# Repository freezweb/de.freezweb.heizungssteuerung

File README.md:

# de.freezweb.heizungssteuerung

Heizungssteuerung auf Revolution Pi Connect 4 mit Anbindung an Home Assistant (MQTT).

Komplette Spezifikation: siehe [LASTENHEFT.md](LASTENHEFT.md).

## Komponenten
- **Hauptsteuerung** Heizungsraum (RevPi #1, `10.1.25.10`)
- **Slave-Steuerung** Hauptkeller (RevPi #2, `10.1.25.11`, sp&auml;ter)
- **Visualisierung + History**: Home Assistant via MQTT-Discovery
- **Failsafe**: Witterungsgef&uuml;hrte Heizkurve bei MQTT-/HA-Ausfall

## Stack
- Python 3.11 (Asyncio)
- `revpimodio2` &mdash; RevPi-I/O
- `paho-mqtt` &mdash; HA-Kopplung
- `pymodbus` &mdash; W&auml;rmepumpen, Klima-Innenger&auml;te, Slave-CPU
- systemd (`Type=simple, Restart=on-failure`)

## Verzeichnisstruktur
```
src/heizung/        Hauptcode
config/             Live-Configs (gitignored, *.example committet)
pictory/            RevPi-PiCtory-Export
tests/              Pytest
deploy/             systemd-Unit + install/update Scripts
docs/               Hydraulik-, I/O- und MQTT-Doku
```

Wichtige Hardware-Planung:
- [docs/revpi-modulplanung.md](docs/revpi-modulplanung.md)
- [docs/io-belegung.md](docs/io-belegung.md)

## Quick start (Entwicklung)
```bash
python -m venv .venv
.venv\Scripts\activate
pip install -e .
cp config/settings.yaml.example config/settings.yaml
# Anpassen, dann:
python -m heizung
```

## Deployment auf RevPi
Siehe `deploy/install.sh`.

## Phasen-Plan
Siehe [LASTENHEFT.md Abschnitt 10](LASTENHEFT.md#10-phasen-plan-reihenfolge).

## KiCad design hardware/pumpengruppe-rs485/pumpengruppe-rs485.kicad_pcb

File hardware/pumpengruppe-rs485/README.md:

# Pumpengruppe RS485 KiCad-Projekt

RevA preliminary, Stand 2026-06-25.

Dieses Verzeichnis enthaelt den KiCad-Startentwurf fuer die dezentrale
Pumpengruppen-Platine:

- `pumpengruppe-rs485.kicad_pro`: KiCad-Projekt
- `pumpengruppe-rs485.kicad_sch`: Schaltplan mit lokalen Symbolen
- `pumpengruppe-rs485.kicad_pcb`: PCB-Grundlayout 160 x 110 mm
- `lib/`: lokale Symbole/Footprints
- `export-fab.ps1`: Gerber/Drill/BOM-Export per `kicad-cli`
- `fab/`: Zielordner fuer Fertigungsdaten

Aktueller Stand:

- Schaltplan/PCB laden in KiCad 10.0.4.
- Schaltplan enthaelt jetzt alle im PCB platzierten Hauptbauteile inklusive
  `F1`, `U5`, USB-C/USB-UART und schaltbarem RS485-Abschluss. Die lokalen
  Symbole haben benannte Pins; die Netznamen sind als sichtbare Texte an den
  Funktionspins gesetzt.
- Gerber/Drill/BOM lassen sich per `export-fab.ps1` erzeugen.
- USB-C-Serviceanschluss mit USB-UART-Funktion ist eingeplant.
- UART-Topologie im Schaltplan ist getrennt:
  `U6` USB-UART liegt nur auf ESP-UART0 (`ESP_U0RX`/`ESP_U0TX`) fuer
  Firmware/Debug. `U4` MAX3485 liegt separat auf dem RS485-UART
  (`RS485_UART_RX` = ESP GPIO16, `RS485_UART_TX` = ESP GPIO17,
  `RS485_DE` = ESP GPIO4). Nach dieser Korrektur muss die PCB-Datei in KiCad
  aus dem Schaltplan aktualisiert und das Routing fuer diese Netze neu gezogen
  werden; alte `UART_RX`/`UART_TX`-Routen im PCB duerfen nicht als
  Fertigungsstand gelten.
- ESP32 ist als WROOM-32D mit PCB-Antenne vorgesehen; Antennenseite am
  Platinenrand platzieren und Keepout freihalten.
- Relais werden nicht direkt vom ESP geschaltet: pro Relais sind 100R
  Gatewiderstand, 100k Pulldown, AO3400A-kompatibler NMOS, SS14-Freilaufdiode
  und Status-LED vorgesehen.
- Mischer ist als Hardware-Interlock geplant: `K2` schaltet nur die
  Mischerfreigabe, `K3` ist ein SPDT-Umschaltrelais fuer die Richtung
  `NC=ZU` / `NO=AUF`. Damit koennen AUF und ZU elektrisch nicht gleichzeitig
  gespeist werden.
- Kontrollanzeigen: 230 V diskret auf der Netzseite mit `R40/R41/D40/D41`,
  5 V, 3V3 sowie RS485 TX/RX und die drei Relaisansteuerungen.
- Adressierbare RGB-Anzeige: `D60-D83` sind einheitliche SK6812MINI/3535-5-V-RGB-LEDs
  an `RGB_DATA`/ESP32 GPIO21. `D60-D63` bleiben allgemeine Status-LEDs,
  `D64-D83` bilden den senkrechten Ventilstand-Balken mit 5-%-Schritten;
  die 20er-Leiste ist im 4,8-mm-Raster gesetzt, damit Courtyards nicht kollidieren.
- RTD/ESP-Hinweis: Die beiden MAX31865 haben getrennte Chip-Select-Leitungen
  (`RTD_VL_CS` = GPIO5, `RTD_RL_CS` = GPIO22). Der ESP32-EN-Pin ist ueber
  `R33` als 10-kOhm-Pullup an `+3V3` angebunden.
- Netzteil ist auf ein guenstiges KiCad-Standardfootprint fuer
  `HLK-5M05`/`HLK-5Mxx` umgestellt.
- RS485 ist auf eine guenstige Standardtransceiver-Schaltung umgestellt:
  `U4` = MAX3485/SP3485-Klasse im SOIC-8 mit getrennten UART-Netzen zum ESP,
  `RS485_DE` vom ESP fuer DE/RE.
- Ueberspannungsschutz auf der Netzseite ist diskret vorgesehen:
  `RV1` als 275-VAC-MOV zwischen L und N.
- RJ45 Pin 1/2 fuehren `BUS_5V`, Pin 7/8 `COM`; `F2` schuetzt die 5V-Kopplung
  mit PTC, `R32` koppelt COM auf lokale 0V fuer RJ45-Power-Sharing.
- Es gibt zwei Bestueckungsvarianten fuer dieselbe Leiterplatte:
  - Vollausbau Pumpengruppe: `pumpengruppe-rs485-bom.csv` und
    `pumpengruppe-rs485-pick-place.csv`.
  - Temperatur-/RS485-Variante: `pumpengruppe-rs485-bom-tempinput.csv` und
    `pumpengruppe-rs485-pick-place-tempinput.csv`; dabei bleibt der linke
    230-V-/Relaisbereich unbestueckt und die Versorgung erfolgt ueber
    `BUS_5V`/RJ45.
- Die Breakaway-Variante ist im Board sichtbar umgesetzt: `MB1` setzt
  0,7-mm-NPTH-Mousebites in die oberen und unteren Materialstege des
  vorhandenen Isolationsschlitzes. Zusaetzlich bleibt die
  `Dwgs.User`-/Silkscreen-Markierung fuer die Bestueckungsvariante erhalten.
- Netzteil und Relais sind so platziert, dass die Bauteile den
  MAINS/SELV-Spalt ueberbruecken: Netz-/Kontaktpins links, SELV-/Spulenpins
  rechts.
- RS485-Abschluss ist schaltbar: `R3 = 120R` in Serie mit `JP1`. `JP1` ist
  ein 1x3-Header, damit der Jumper am Geraet bleiben kann:
  `1-2 = Abschluss aktiv`, `2-3 = Parkposition/Aus`.
- RJ45-Buchsen und USB-C-Serviceport sind an die Unterkante gesetzt und zeigen
  zur Kante, damit Stecker/Kabel nutzbar sind. RS485-Schraubklemmen bleiben an
  der rechten Anschlusskante. J3/J4 sind auf dem Silkscreen mit A/B/GND
  beschriftet; am unteren Rand steht das RJ45-Pinout
  `1/2=5V 3/6=NC 4=A 5=B 7/8=GND`.
- KiCad-Netclasses sind in `pumpengruppe-rs485.kicad_pro` gesetzt:
  `230V` routet L/N/geschaltete 230-V-Lastnetze und PE mit 1,5 mm und
  0,8 mm Clearance innerhalb der 230-V-Netze. Fuer die 5-A-Sicherung sollte die
  Bestellung mit mindestens 70 um / 2 oz Kupfer angefragt werden oder die
  tatsaechliche Last/Sicherung entsprechend reduziert werden. Die 8-mm-Trennung
  zwischen 230 V und SELV bleibt als physische Keepout-/Fraesnut-Regel beim
  Layout zwingend einzuhalten.
- Die Netclasses fuer weitere Power-Routings sind gesetzt:
  `SELV_POWER_0V8` fuer `+5V`, `BUS_5V`, `USB_VBUS`, `GND` und `RS485_GND`;
  `Doppelte Dicke` mit 0,4 mm fuer `+3V3`. Auf der RGB-/Temp-Input-Seite sind
  erste vorhandene 5-V-/GND-Segmente real auf 0,8 mm und 3V3-Segmente auf
  0,4 mm verbreitert. Einige Engstellen an USB/RJ45 bleiben bewusst 0,2 mm,
  weil breitere Leiterbahnen dort DRC-Kurzschluesse erzeugen wuerden. Fuer die
  finale Serienplatine sollten diese Netze weiter gezielt als breite
  Versorgungsstaemme bzw. Kupferflaechen nachgezogen werden.

Wichtig: RevA ist elektrisch geroutet und hat keine offenen Netze im KiCad-DRC.
Vor einer Netzspannungs-Freigabe bleiben trotzdem Relais-/Sicherungsrating,
PE-Fuehrung, Gehaeuseintegration, Beruehrschutz, EMV-Schutz und die
Herstellerfreigabe fuer 230-V-Abstaende zu pruefen. Wenn die RJ45-5V-Weitergabe
bestueckt/genutzt wird, ist die RS485-/SELV-Masse gemeinsam; das
Isolationskonzept muss dann als gemeinsamer SELV-Bus bewertet werden.

## Export

Nach Installation von KiCad:

```powershell
cd hardware\pumpengruppe-rs485
.\export-fab.ps1
```

Das Skript erzeugt Gerber, Excellon-Drill, beide BOM-Varianten, beide
Pick-and-Place/XY-Dateien und eine ZIP-Datei in `fab/`.

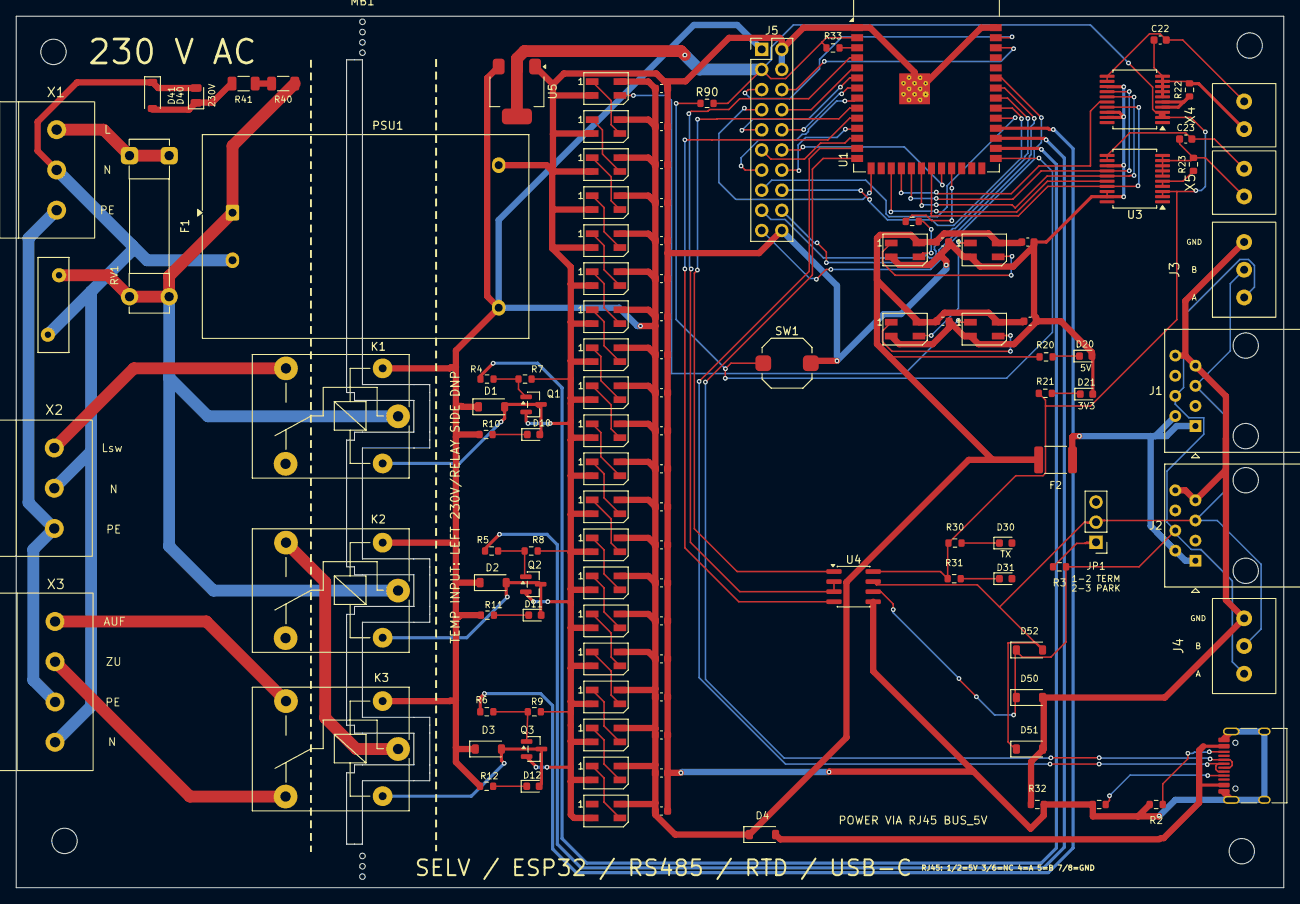
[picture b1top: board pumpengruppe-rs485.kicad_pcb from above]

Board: 2 copper layers, 160.0 x 110.0 mm, 123 parts (0 on the bottom side), 95 nets.

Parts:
C22, C23: 10nF 50V; C_0603_1608Metric
C60, C61, C62, C63, C64, C65, C66, C67, C68, C69, C70, C71, C72, C73, C74, C75, C76, C77, C78, C79, C80, C81, C82, C83: 100nF 16V; C_0603_1608Metric
D1, D2, D3, D4: B5819W; D_SOD-123
D10, D11, D12, D20, D21, D30, D31: LED green 0603; LED_0603_1608Metric
D40: LED green 0805; LED_0805_2012Metric
D41: 1N4148W; D_SOD-123
D50, D51, D52: DNP TVS SOD-123; D_SOD-123
D60, D61, D62, D63, D64, D65, D66, D67, D68, D69, D70, D71, D72, D73, D74, D75, D76, D77, D78, D79, D80, D81, D82, D83: SK6812MINI-E; LED_SK6812MINI_PLCC4_3.5x3.5mm_P1.75mm
F1: 2x FC-203-22 fuse clips for 5x20; Fuseholder_Clip-5x20mm_Bel_FC-203-22_Lateral_P17.80x5.00mm_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
F2: PTC 1.1A 1812; Fuse_1812_4532Metric
H1, H2, H3, H4: MountingHole_M3; MountingHole_3.2mm_M3
J1, J2: RJ45 8P8C horizontal; RJ45_Amphenol_54602-x08_Horizontal
J3, J4: KF128L-3.5-3P; TB_KF128L_350_3P
J5: EXT_GPIO_HEADER; PinHeader_2x10_P2.54mm_Vertical
JP1: 1x3 2.54mm header; PinHeader_1x03_P2.54mm_Vertical
K1, K2, K3: SRD-05VDC-SL-C; Relay_SPDT_SANYOU_SRD_Series_Form_C
MB1: BREAKAWAY_MOUSEBITES
PSU1: HLK-5M05; Converter_ACDC_Hi-Link_HLK-5Mxx
Q1, Q2, Q3: AO3400A; SOT-23
R1, R2: 5.1k 1% 0603; R_0603_1608Metric
R3: 120R 1% 0603; R_0603_1608Metric
R4, R5, R6: 100R 1% 0603; R_0603_1608Metric
R7, R8, R9: 100k 1% 0603; R_0603_1608Metric
R10, R11, R12, R20: 2.2k 1% 0603; R_0603_1608Metric
R21: 1.5k 1% 0603; R_0603_1608Metric
R22, R23: 4.3k 0.1% 0603; R_0603_1608Metric
R30, R31: 4.7k 1% 0603; R_0603_1608Metric
R32: 0R 0603; R_0603_1608Metric
R33, R90: 10k 1% 0603; R_0603_1608Metric
R40, R41: 150k 1% 1206; R_1206_3216Metric
R60: 330R 1% 0603; R_0603_1608Metric
RV1: MOV 275VAC; RV_Disc_D12mm_W3.9mm_P7.5mm
SW1: BOOT/CFG RESET; SW_Push_1TS009xxxx-xxxx-xxxx_6x6x5mm
U1: ESP32-S3-WROOM-1-N4; ESP32-S3-WROOM-1
U2, U3: MAX31865AAP+; SSOP-20_5.3x7.2mm_P0.65mm
U4: SP3485EN-L/TR; SOIC-8_3.9x4.9mm_P1.27mm
U5: AMS1117-3.3; SOT-223-3_TabPin2
X1, X2: KF128-5.08-3P-AA; TB_KF128_508_3P
X3: DB128L-5.08-4P-GN-S; TB_DB128L_508_4P
X4, X5: KF128L-3.5-2P; TB_KF128L_350_2P
X6: USB-C receptacle; USB_C_Receptacle_HRO_TYPE-C-31-M-12

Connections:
/+3V3: J5.3, R21.1, R30.1, R31.1, R33.1, R90.2, U1.2, U2.2 (DVDD), U2.3 (VDD), U3.2 (DVDD), U3.3 (VDD), U4.8 (VCC), U5.2 (VO)
/+5V: C60.1, C61.1, C62.1, C63.1, C64.1, C65.1, C66.1, C67.1, C68.1, C69.1, C70.1, C71.1, C72.1, C73.1, C74.1, C75.1, C76.1, C77.1, C78.1, C79.1, C80.1, C81.1, C82.1, C83.1, D1.1 (K), D2.1 (K), D3.1 (K), D4.1 (K), D60.4 (VDD), D61.4 (VDD), D62.4 (VDD), D63.4 (VDD), D64.4 (VDD), D65.4 (VDD), D66.4 (VDD), D67.4 (VDD), D68.4 (VDD), D69.4 (VDD), D70.4 (VDD), D71.4 (VDD), D72.4 (VDD), D73.4 (VDD), D74.4 (VDD), D75.4 (VDD), D76.4 (VDD), D77.4 (VDD), D78.4 (VDD), D79.4 (VDD), D80.4 (VDD), D81.4 (VDD), D82.4 (VDD), D83.4 (VDD), F2.2, J5.1, K1.2, K2.2, K3.2, PSU1.4 (+Vout), R10.1, R11.1, R12.1, R20.1, U5.3 (VI)
/BUS_5V: F2.1, J1.1, J1.2, J2.1, J2.2
/ESP_EN: R33.2, U1.3
/ESP_IO0_BOOT: R90.1, SW1.1, U1.27
/ESP_IO1_EXT: J5.5, U1.39
/ESP_IO2_EXT: J5.6, U1.38
/ESP_IO3_EXT: J5.7, U1.15
/ESP_IO5_EXT: J5.8, U1.5
/ESP_IO6_EXT: J5.9, U1.6
/ESP_IO7_EXT: J5.10, U1.7
/ESP_IO8_EXT: J5.11, U1.12
/ESP_IO14_EXT: J5.12, U1.22
/ESP_IO15_EXT: J5.13, U1.8
/ESP_IO18_EXT: J5.14, U1.11
/ESP_IO38_EXT: J5.15, U1.31
/ESP_IO39_EXT: J5.16, U1.32
/ESP_IO40_EXT: J5.17, U1.33
/ESP_IO41_EXT: J5.18, U1.34
/ESP_IO42_EXT: J5.19, U1.35
/GND: C60.2, C61.2, C62.2, C63.2, C64.2, C65.2, C66.2, C67.2, C68.2, C69.2, C70.2, C71.2, C72.2, C73.2, C74.2, C75.2, C76.2, C77.2, C78.2, C79.2, C80.2, C81.2, C82.2, C83.2, D20.2 (A), D21.2 (A), D60.2 (VSS), D61.2 (VSS), D62.2 (VSS), D63.2 (VSS), D64.2 (VSS), D65.2 (VSS), D66.2 (VSS), D67.2 (VSS), D68.2 (VSS), D69.2 (VSS), D70.2 (VSS), D71.2 (VSS), D72.2 (VSS), D73.2 (VSS), D74.2 (VSS), D75.2 (VSS), D76.2 (VSS), D77.2 (VSS), D78.2 (VSS), D79.2 (VSS), D80.2 (VSS), D81.2 (VSS), D82.2 (VSS), D83.2 (VSS), J5.2, J5.4, J5.20, PSU1.3 (-Vout), Q1.2 (D), Q2.2 (D), Q3.2 (D), R1.2, R2.2, R7.2, R8.2, R9.2, R32.2, SW1.2, U1.1, U1.40, U1.41, U2.13 (GND), U2.18 (DGND), U2.19 (GND), U3.13 (GND), U3.18 (DGND), U3.19 (GND), U4.5 (GND), U5.1 (GND), X6.A1 (GND), X6.A12 (GND), X6.B1 (GND), X6.B12 (GND), X6.SH (SHIELD)
/LED_3V3_K: D21.1 (K), R21.2
/LED_5V_K: D20.1 (K), R20.2
/LED_MIX_DIR_K: D12.1 (K), R12.2
/LED_MIX_ENABLE_K: D11.1 (K), R11.2
/LED_PUMP_K: D10.1 (K), R10.2
/LED_USB_RX_K: D31.1 (K), R31.2
/LED_USB_TX_K: D30.1 (K), R30.2
/L_FUSED: F1.2, K1.1, K2.1, PSU1.1 (AC/L), R40.1, RV1.1
/L_IN: F1.1, X1.1
/L_MIX_CLOSE: K3.4, X3.2
/L_MIX_ENABLE: K2.3, K3.1
/L_MIX_OPEN: K3.3, X3.1
/L_PUMP: K1.3, X2.1
/MAINS_LED_K: D40.1 (K), D41.2 (A), R41.2
/MAINS_LED_SERIES: R40.2, R41.1
/MIX_DIR_COIL_DRV: D3.2 (A), D12.2 (A), K3.5, Q3.3 (S)
/MIX_DIR_DRV: Q3.1 (G), R6.2, R9.1
/MIX_DIR_DRV_GPIO: R6.1, U1.30
/MIX_ENABLE_COIL_DRV: D2.2 (A), D11.2 (A), K2.5, Q2.3 (S)
/MIX_ENABLE_DRV: Q2.1 (G), R5.2, R8.1
/MIX_ENABLE_DRV_GPIO: R5.1, U1.29
/N: D40.2 (A), D41.1 (K), PSU1.2 (AC/N), RV1.2, X1.2, X2.2, X3.4
/PE: X1.3, X2.3, X3.3
/PUMP_COIL_DRV: D1.2 (A), D10.2 (A), K1.5, Q1.3 (S)
/PUMP_DRV: Q1.1 (G), R4.2, R7.1
/PUMP_DRV_GPIO: R4.1, U1.28
/RGB_D60_DIN: D60.3 (DIN), R60.2
/RGB_D60_DOUT: D60.1 (DOUT), D61.3 (DIN)
/RGB_D61_DOUT: D61.1 (DOUT), D62.3 (DIN)
/RGB_D62_DOUT: D62.1 (DOUT), D63.3 (DIN)
/RGB_D63_DOUT: D63.1 (DOUT), D64.3 (DIN)
/RGB_D64_DOUT: D64.1 (DOUT), D65.3 (DIN)
/RGB_D65_DOUT: D65.1 (DOUT), D66.3 (DIN)
/RGB_D66_DOUT: D66.1 (DOUT), D67.3 (DIN)
/RGB_D67_DOUT: D67.1 (DOUT), D68.3 (DIN)
/RGB_D68_DOUT: D68.1 (DOUT), D69.3 (DIN)
/RGB_D69_DOUT: D69.1 (DOUT), D70.3 (DIN)
/RGB_D70_DOUT: D70.1 (DOUT), D71.3 (DIN)
/RGB_D71_DOUT: D71.1 (DOUT), D72.3 (DIN)
/RGB_D72_DOUT: D72.1 (DOUT), D73.3 (DIN)
/RGB_D73_DOUT: D73.1 (DOUT), D74.3 (DIN)
/RGB_D74_DOUT: D74.1 (DOUT), D75.3 (DIN)
/RGB_D75_DOUT: D75.1 (DOUT), D76.3 (DIN)
/RGB_D76_DOUT: D76.1 (DOUT), D77.3 (DIN)
/RGB_D77_DOUT: D77.1 (DOUT), D78.3 (DIN)
/RGB_D78_DOUT: D78.1 (DOUT), D79.3 (DIN)
/RGB_D79_DOUT: D79.1 (DOUT), D80.3 (DIN)
/RGB_D80_DOUT: D80.1 (DOUT), D81.3 (DIN)
/RGB_D81_DOUT: D81.1 (DOUT), D82.3 (DIN)
/RGB_D82_DOUT: D82.1 (DOUT), D83.3 (DIN)
/RGB_DATA: R60.1, U1.23
/RS485_A: D50.1 (A1), D52.1 (A1), J1.4, J2.4, J3.1, J4.1, R3.1, U4.6 (A)
/RS485_B: D51.1 (A1), D52.2 (A2), J1.5, J2.5, J3.2, J4.2, JP1.2, U4.7 (B)
/RS485_DE: U1.4, U4.2 (~RE), U4.3 (DE)
/RS485_GND: D50.2 (A2), D51.2 (A2), J1.7, J1.8, J2.7, J2.8, J3.3, J4.3, R32.1
/RS485_TERM: JP1.1, R3.2
/RS485_UART_RX: U1.9, U4.1 (RO)
/RS485_UART_TX: U1.10, U4.4 (DI)
/RTD_RL_BIAS: R23.1, U3.4 (BIAS), U3.5 (REFIN+)
/RTD_RL_CS: U1.17, U3.16 (~CS)
/RTD_RL_FORCE_MINUS: C23.2, U3.11 (RTDIN-), U3.12 (FORCE-), X5.2
/RTD_RL_FORCE_PLUS: C23.1, R23.2, U3.6 (REFIN-), U3.7 (ISENSOR), U3.8 (FORCE+), U3.9 (FORCE2), U3.10 (RTDIN+), X5.1
/RTD_VL_BIAS: R22.1, U2.4 (BIAS), U2.5 (REFIN+)
/RTD_VL_CS: U1.18, U2.16 (~CS)
/RTD_VL_FORCE_MINUS: C22.2, U2.11 (RTDIN-), U2.12 (FORCE-), X4.2
/RTD_VL_FORCE_PLUS: C22.1, R22.2, U2.6 (REFIN-), U2.7 (ISENSOR), U2.8 (FORCE+), U2.9 (FORCE2), U2.10 (RTDIN+), X4.1
/SPI_MISO: U1.21, U2.17 (SDO), U3.17 (SDO)
/SPI_MOSI: U1.19, U2.14 (SDI), U3.14 (SDI)
/SPI_SCK: U1.20, U2.15 (SCLK), U3.15 (SCLK)
/USB_CC1: R1.1, X6.A5 (CC1)
/USB_CC2: R2.1, X6.B5 (CC2)
/USB_D+: U1.14, X6.A6 (D+), X6.B6 (D+)
/USB_D-: U1.13, X6.A7 (D-), X6.B7 (D-)
/USB_VBUS: D4.2 (A), X6.A4 (VBUS), X6.A9 (VBUS), X6.B4 (VBUS), X6.B9 (VBUS)

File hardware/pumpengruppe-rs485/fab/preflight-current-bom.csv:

"Refs","Value","Footprint","Qty","DNP"
"C22","10nF 50V","Capacitor_SMD:C_0603_1608Metric","1",""
"C23","10nF 50V","Capacitor_SMD:C_0603_1608Metric","1",""
"C60","100nF 16V","Capacitor_SMD:C_0603_1608Metric","1",""
"C61","100nF 16V","Capacitor_SMD:C_0603_1608Metric","1",""
"C62","100nF 16V","Capacitor_SMD:C_0603_1608Metric","1",""
"C63","100nF 16V","Capacitor_SMD:C_0603_1608Metric","1",""
"C64","100nF 16V","Capacitor_SMD:C_0603_1608Metric","1",""
"C65","100nF 16V","Capacitor_SMD:C_0603_1608Metric","1",""
"C66","100nF 16V","Capacitor_SMD:C_0603_1608Metric","1",""
"C67","100nF 16V","Capacitor_SMD:C_0603_1608Metric","1",""
"C68","100nF 16V","Capacitor_SMD:C_0603_1608Metric","1",""
"C69","100nF 16V","Capacitor_SMD:C_0603_1608Metric","1",""
"C70","100nF 16V","Capacitor_SMD:C_0603_1608Metric","1",""
"C71","100nF 16V","Capacitor_SMD:C_0603_1608Metric","1",""
"C72","100nF 16V","Capacitor_SMD:C_0603_1608Metric","1",""
"C73","100nF 16V","Capacitor_SMD:C_0603_1608Metric","1",""
"C74","100nF 16V","Capacitor_SMD:C_0603_1608Metric","1",""
"C75","100nF 16V","Capacitor_SMD:C_0603_1608Metric","1",""
"C76","100nF 16V","Capacitor_SMD:C_0603_1608Metric","1",""
"C77","100nF 16V","Capacitor_SMD:C_0603_1608Metric","1",""
"C78","100nF 16V","Capacitor_SMD:C_0603_1608Metric","1",""
"C79","100nF 16V","Capacitor_SMD:C_0603_1608Metric","1",""
"C80","100nF 16V","Capacitor_SMD:C_0603_1608Metric","1",""
"C81","100nF 16V","Capacitor_SMD:C_0603_1608Metric","1",""
"C82","100nF 16V","Capacitor_SMD:C_0603_1608Metric","1",""
"C83","100nF 16V","Capacitor_SMD:C_0603_1608Metric","1",""
"D1","B5819W","Diode_SMD:D_SOD-123","1",""
"D2","B5819W","Diode_SMD:D_SOD-123","1",""
"D3","B5819W","Diode_SMD:D_SOD-123","1",""
"D4","B5819W","Diode_SMD:D_SOD-123","1",""
"D10","LED green 0603","LED_SMD:LED_0603_1608Metric","1",""
"D11","LED green 0603","LED_SMD:LED_0603_1608Metric","1",""
"D12","LED green 0603","LED_SMD:LED_0603_1608Metric","1",""
"D20","LED green 0603","LED_SMD:LED_0603_1608Metric","1",""
"D21","LED green 0603","LED_SMD:LED_0603_1608Metric","1",""
"D30","LED green 0603","LED_SMD:LED_0603_1608Metric","1",""
"D31","LED green 0603","LED_SMD:LED_0603_1608Metric","1",""
"D40","LED green 0805","LED_SMD:LED_0805_2012Metric","1",""
"D41","1N4148W","Diode_SMD:D_SOD-123","1",""
"D60","SK6812MINI-E","LED_SMD:LED_SK6812MINI_PLCC4_3.5x3.5mm_P1.75mm","1",""
"D61","SK6812MINI-E","LED_SMD:LED_SK6812MINI_PLCC4_3.5x3.5mm_P1.75mm","1",""
"D62","SK6812MINI-E","LED_SMD:LED_SK6812MINI_PLCC4_3.5x3.5mm_P1.75mm","1",""
"D63","SK6812MINI-E","LED_SMD:LED_SK6812MINI_PLCC4_3.5x3.5mm_P1.75mm","1",""
"D64","SK6812MINI-E","LED_SMD:LED_SK6812MINI_PLCC4_3.5x3.5mm_P1.75mm","1",""
"D65","SK6812MINI-E","LED_SMD:LED_SK6812MINI_PLCC4_3.5x3.5mm_P1.75mm","1",""
"D66","SK6812MINI-E","LED_SMD:LED_SK6812MINI_PLCC4_3.5x3.5mm_P1.75mm","1",""
"D67","SK6812MINI-E","LED_SMD:LED_SK6812MINI_PLCC4_3.5x3.5mm_P1.75mm","1",""
"D68","SK6812MINI-E","LED_SMD:LED_SK6812MINI_PLCC4_3.5x3.5mm_P1.75mm","1",""
"D69","SK6812MINI-E","LED_SMD:LED_SK6812MINI_PLCC4_3.5x3.5mm_P1.75mm","1",""
"D70","SK6812MINI-E","LED_SMD:LED_SK6812MINI_PLCC4_3.5x3.5mm_P1.75mm","1",""
"D71","SK6812MINI-E","LED_SMD:LED_SK6812MINI_PLCC4_3.5x3.5mm_P1.75mm","1",""
"D72","SK6812MINI-E","LED_SMD:LED_SK6812MINI_PLCC4_3.5x3.5mm_P1.75mm","1",""
"D73","SK6812MINI-E","LED_SMD:LED_SK6812MINI_PLCC4_3.5x3.5mm_P1.75mm","1",""
"D74","SK6812MINI-E","LED_SMD:LED_SK6812MINI_PLCC4_3.5x3.5mm_P1.75mm","1",""
"D75","SK6812MINI-E","LED_SMD:LED_SK6812MINI_PLCC4_3.5x3.5mm_P1.75mm","1",""
"D76","SK6812MINI-E","LED_SMD:LED_SK6812MINI_PLCC4_3.5x3.5mm_P1.75mm","1",""
"D77","SK6812MINI-E","LED_SMD:LED_SK6812MINI_PLCC4_3.5x3.5mm_P1.75mm","1",""
"D78","SK6812MINI-E","LED_SMD:LED_SK6812MINI_PLCC4_3.5x3.5mm_P1.75mm","1",""
"D79","SK6812MINI-E","LED_SMD:LED_SK6812MINI_PLCC4_3.5x3.5mm_P1.75mm","1",""
"D80","SK6812MINI-E","LED_SMD:LED_SK6812MINI_PLCC4_3.5x3.5mm_P1.75mm","1",""
"D81","SK6812MINI-E","LED_SMD:LED_SK6812MINI_PLCC4_3.5x3.5mm_P1.75mm","1",""
"D82","SK6812MINI-E","LED_SMD:LED_SK6812MINI_PLCC4_3.5x3.5mm_P1.75mm","1",""
"D83","SK6812MINI-E","LED_SMD:LED_SK6812MINI_PLCC4_3.5x3.5mm_P1.75mm","1",""
"F1","5x20 fuse holder","FW_Pumpengruppe:FUSE_5X20","1",""
"F2","PTC 1.1A 1812","Fuse:Fuse_1812_4532Metric","1",""
"J1","RJ45 8P8C horizontal","Connector_RJ:RJ45_Amphenol_54602-x08_Horizontal","1",""
"J2","RJ45 8P8C horizontal","Connector_RJ:RJ45_Amphenol_54602-x08_Horizontal","1",""
"J3","KF128L-3.5-3P","FW_Pumpengruppe:TB_KF128L_350_3P","1",""
"J4","KF128L-3.5-3P","FW_Pumpengruppe:TB_KF128L_350_3P","1",""
"J5","EXT_GPIO_HEADER","Connector_PinHeader_2.54mm:PinHeader_2x10_P2.54mm_Vertical","1",""
"JP1","1x3 2.54mm header","Connector_PinHeader_2.54mm:PinHeader_1x03_P2.54mm_Vertical","1",""
"K1","SRD-05VDC-SL-C","Relay_THT:Relay_SPDT_SANYOU_SRD_Series_Form_C","1",""
"K2","SRD-05VDC-SL-C","Relay_THT:Relay_SPDT_SANYOU_SRD_Series_Form_C","1",""
"K3","SRD-05VDC-SL-C","Relay_THT:Relay_SPDT_SANYOU_SRD_Series_Form_C","1",""
"PSU1","HLK-5M05","Converter_ACDC:Converter_ACDC_Hi-Link_HLK-5Mxx","1",""
"Q1","AO3400A","Package_TO_SOT_SMD:SOT-23","1",""
"Q2","AO3400A","Package_TO_SOT_SMD:SOT-23","1",""
"Q3","AO3400A","Package_TO_SOT_SMD:SOT-23","1",""
"R1","5.1k 1% 0603","Resistor_SMD:R_0603_1608Metric","1",""
"R2","5.1k 1% 0603","Resistor_SMD:R_0603_1608Metric","1",""
"R4","100R 1% 0603","Resistor_SMD:R_0603_1608Metric","1",""
"R5","100R 1% 0603","Resistor_SMD:R_0603_1608Metric","1",""
"R6","100R 1% 0603","Resistor_SMD:R_0603_1608Metric","1",""
"R7","100k 1% 0603","Resistor_SMD:R_0603_1608Metric","1",""
"R8","100k 1% 0603","Resistor_SMD:R_0603_1608Metric","1",""
"R9","100k 1% 0603","Resistor_SMD:R_0603_1608Metric","1",""
"R10","2.2k 1% 0603","Resistor_SMD:R_0603_1608Metric","1",""
"R11","2.2k 1% 0603","Resistor_SMD:R_0603_1608Metric","1",""
"R12","2.2k 1% 0603","Resistor_SMD:R_0603_1608Metric","1",""
"R20","2.2k 1% 0603","Resistor_SMD:R_0603_1608Metric","1",""
"R21","1.5k 1% 0603","Resistor_SMD:R_0603_1608Metric","1",""
"R22","4.3k 0.1% 0603","Resistor_SMD:R_0603_1608Metric","1",""
"R23","4.3k 0.1% 0603","Resistor_SMD:R_0603_1608Metric","1",""
"R30","4.7k 1% 0603","Resistor_SMD:R_0603_1608Metric","1",""
"R31","4.7k 1% 0603","Resistor_SMD:R_0603_1608Metric","1",""
"R32","0R 0603","Resistor_SMD:R_0603_1608Metric","1",""
"R33","10k 1% 0603","Resistor_SMD:R_0603_1608Metric","1",""
"R40","150k 1% 1206","Resistor_SMD:R_1206_3216Metric","1",""
"R41","150k 1% 1206","Resistor_SMD:R_1206_3216Metric","1",""
"R60","330R 1% 0603","Resistor_SMD:R_0603_1608Metric","1",""
"R90","10k 1% 0603","Resistor_SMD:R_0603_1608Metric","1",""
"RV1","MOV 275VAC","Varistor:RV_Disc_D12mm_W3.9mm_P7.5mm","1",""
"SW1","BOOT/CFG RESET","Button_Switch_SMD:SW_Push_1TS009xxxx-xxxx-xxxx_6x6x5mm","1",""
"U1","ESP32-S3-WROOM-1-N4","RF_Module:ESP32-S3-WROOM-1","1",""
"U2","MAX31865AAP+","Package_SO:SSOP-20_5.3x7.2mm_P0.65mm","1",""
"U3","MAX31865AAP+","Package_SO:SSOP-20_5.3x7.2mm_P0.65mm","1",""
"U4","MAX3485EESA+","Package_SO:SOIC-8_3.9x4.9mm_P1.27mm","1",""
"U5","AMS1117-3.3","Package_TO_SOT_SMD:SOT-223-3_TabPin2","1",""
"X1","KF128-5.08-3P-AA","FW_Pumpengruppe:TB_KF128_508_3P","1",""
"X2","KF128-5.08-3P-AA","FW_Pumpengruppe:TB_KF128_508_3P","1",""
"X3","DB128L-5.08-4P-GN-S","FW_Pumpengruppe:TB_DB128L_508_4P","1",""
"X4","KF128L-3.5-2P","FW_Pumpengruppe:TB_KF128L_350_2P","1",""
"X5","KF128L-3.5-2P","FW_Pumpengruppe:TB_KF128L_350_2P","1",""
"X6","USB-C receptacle","Connector_USB:USB_C_Receptacle_HRO_TYPE-C-31-M-12","1",""

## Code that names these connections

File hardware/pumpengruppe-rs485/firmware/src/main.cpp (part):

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namespace HwPin {
static constexpr uint8_t RS485_RX = 16;
static constexpr uint8_t RS485_TX = 17;
static constexpr uint8_t RS485_DE = 4;
static constexpr uint8_t PUMP_DRV = 35;
static constexpr uint8_t MIX_ENABLE_DRV = 36;
static constexpr uint8_t MIX_DIR_DRV = 37;
static constexpr uint8_t RGB_DATA = 21;
static constexpr uint8_t RGB_COUNT = 24;
static constexpr uint8_t SPI_MOSI = 11;
static constexpr uint8_t SPI_MISO = 13;
static constexpr uint8_t SPI_SCK = 12;
static constexpr uint8_t RTD_VL_CS = 10;
static constexpr uint8_t RTD_RL_CS = 9;
static constexpr uint8_t CONFIG_RESET_BTN = 0;
}

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DNSServer dnsServer;
HardwareSerial rs485(2);
Adafruit_NeoPixel *pixels = nullptr;
Adafruit_MAX31865 rtdVl(HwPin::RTD_VL_CS, HwPin::SPI_MOSI, HwPin::SPI_MISO, HwPin::SPI_SCK);
Adafruit_MAX31865 rtdRl(HwPin::RTD_RL_CS, HwPin::SPI_MOSI, HwPin::SPI_MISO, HwPin::SPI_SCK);
WiFiServer *modbusTcpServer = nullptr;
WiFiClient modbusTcpClients[4];
WiFiClient mqttWifiClient;
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}

static void applyOutputs() {
  digitalWrite(HwPin::PUMP_DRV, st.pumpOn ? HIGH : LOW);
  digitalWrite(HwPin::MIX_DIR_DRV, st.moveDirection > 0 ? HIGH : LOW);
  digitalWrite(HwPin::MIX_ENABLE_DRV, st.moving ? HIGH : LOW);
}

static void allOutputsOff() {
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    delete pixels;
    pixels = nullptr;
  }
  pixels = new Adafruit_NeoPixel(HwPin::RGB_COUNT, HwPin::RGB_DATA, NEO_GRB + NEO_KHZ800);
  pixels->begin();
  pixels->clear();
  pixels->show();
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}

static void rs485Send(const uint8_t *data, size_t len) {
  digitalWrite(HwPin::RS485_DE, HIGH);
  delayMicroseconds(50);
  rs485.write(data, len);
  rs485.flush();
  delayMicroseconds(100);
  digitalWrite(HwPin::RS485_DE, LOW);
  st.txCount++;
}

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
static void setupPins() {
  pinMode(HwPin::CONFIG_RESET_BTN, INPUT_PULLUP);
  pinMode(HwPin::PUMP_DRV, OUTPUT);
  pinMode(HwPin::MIX_ENABLE_DRV, OUTPUT);
  pinMode(HwPin::MIX_DIR_DRV, OUTPUT);
  pinMode(HwPin::RS485_DE, OUTPUT);
  digitalWrite(HwPin::RS485_DE, LOW);
  allOutputsOff();
}

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
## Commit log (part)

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2026-06-16 sicherung
2026-06-26 icherung
